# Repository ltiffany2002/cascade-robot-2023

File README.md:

# cascade-robot-2023
Code and PCB board for Cascade 2023 Robotics: Introduction to EE and Microcontrollers

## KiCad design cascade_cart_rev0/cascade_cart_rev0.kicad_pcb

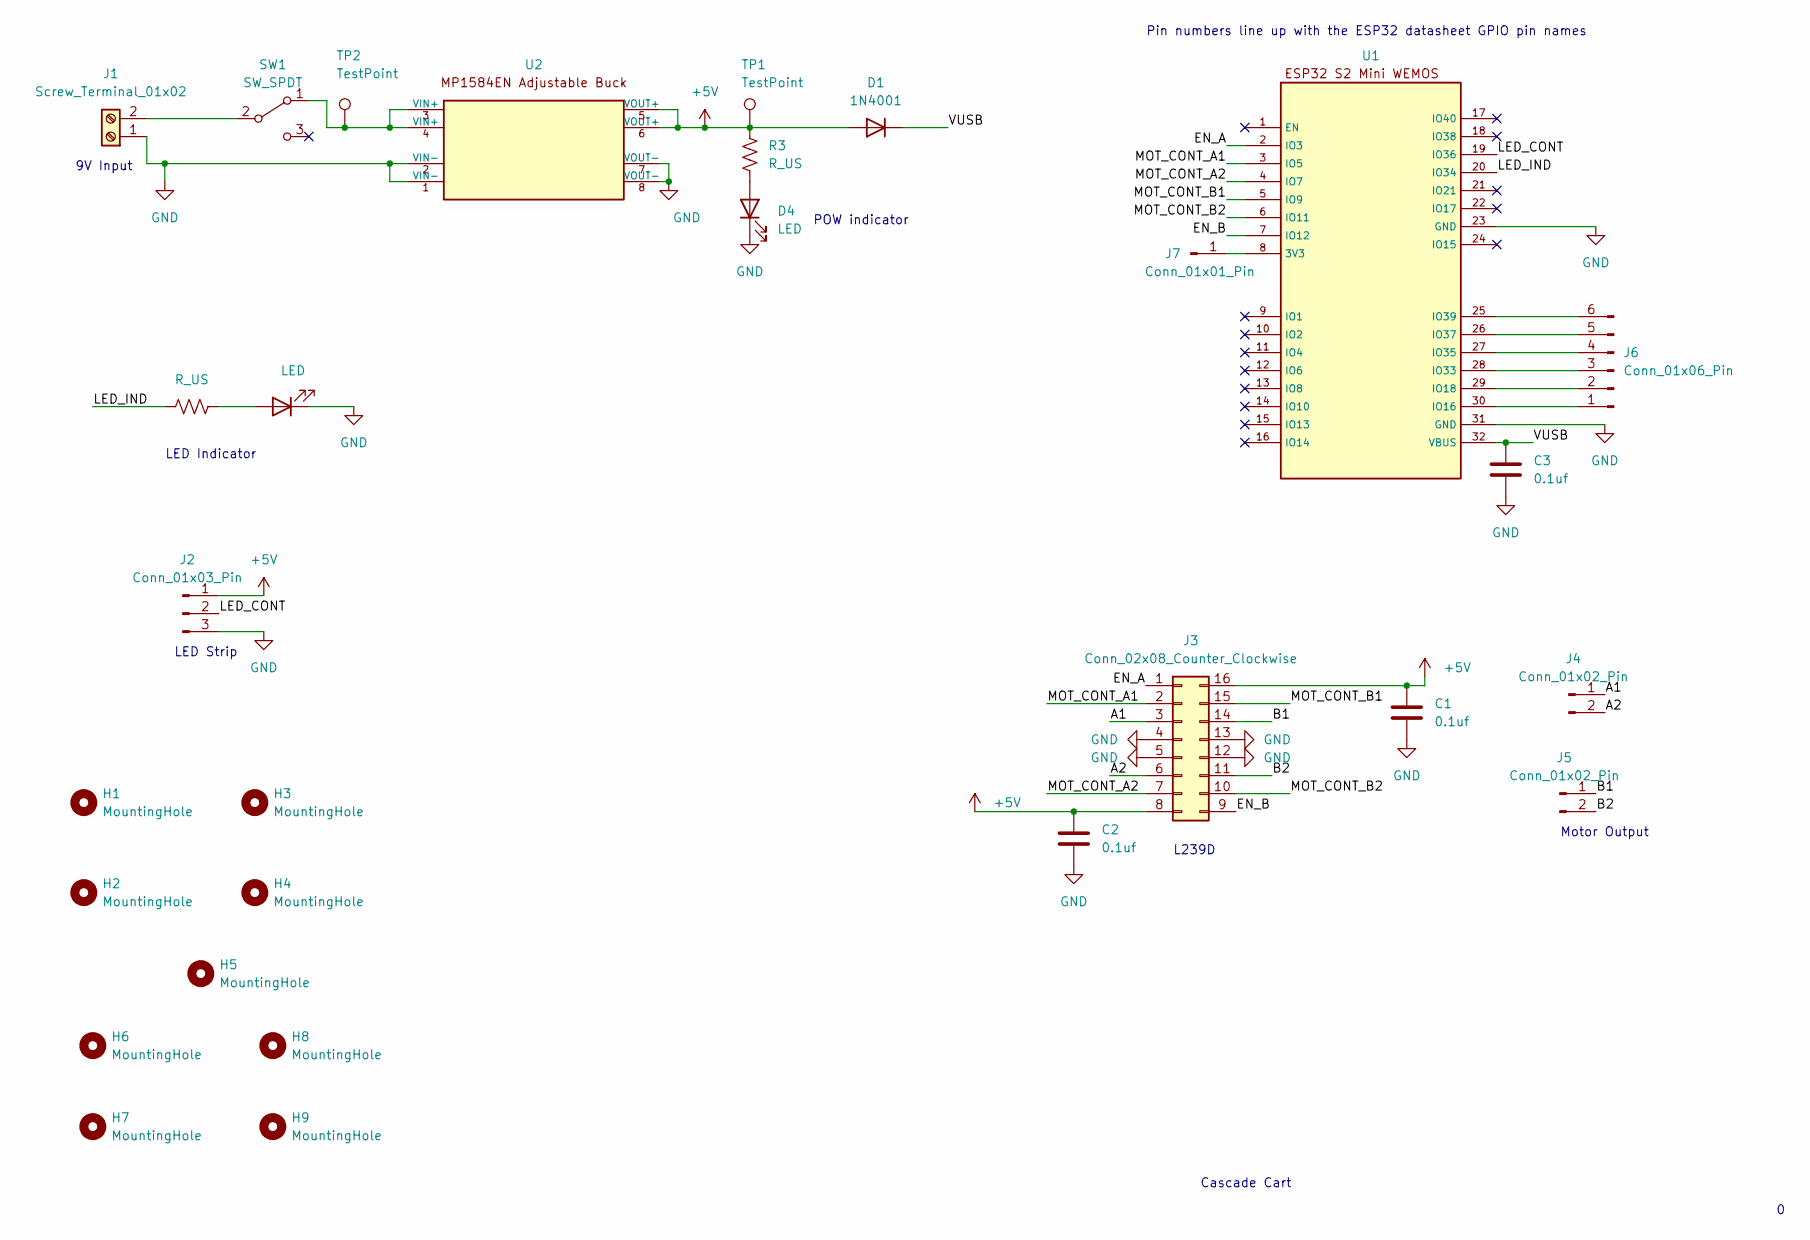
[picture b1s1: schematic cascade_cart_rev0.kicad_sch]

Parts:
C1, C2, C3: 0.1uf; C_Disc_D4.3mm_W1.9mm_P5.00mm
D1: 1N4001; D_DO-41_SOD81_P10.16mm_Horizontal
D3, D4: LED; LED_D5.0mm
H1, H2, H3, H4, H5, H6, H7, H8, H9: MountingHole; MountingHole_3.2mm_M3
J1: Screw_Terminal_01x02; PinHeader_1x02_P2.54mm_Vertical
J2: Conn_01x03_Pin; PinSocket_1x03_P2.54mm_Vertical
J3: Conn_02x08_Counter_Clockwise; 16-DIP Package
J4, J5: Conn_01x02_Pin; PinSocket_1x02_P2.54mm_Vertical
J6: Conn_01x06_Pin; PinHeader_1x06_P2.54mm_Vertical
J7: Conn_01x01_Pin; PinHeader_1x01_P2.54mm_Vertical
R2, R3: R_US; R_Axial_DIN0207_L6.3mm_D2.5mm_P10.16mm_Horizontal
SW1: SW_SPDT; PinSocket_1x03_P2.54mm_Vertical
TP1, TP2: TestPoint; TestPoint_Pad_D2.5mm
U1: esp32-s2-mini
U2: buck-breakout

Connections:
+5V: C1.1, C2.1, D1.2 (A), J2.1, J3.8, J3.16, R3.1, TP1.1, U2.5 (VOUT+), U2.6 (VOUT+)
/A1: J3.3, J4.1
/A2: J3.6, J4.2
/B1: J3.14, J5.1
/B2: J3.11, J5.2
/EN_A: J3.1, U1.2 (IO3)
/EN_B: J3.9, U1.7 (IO12)
/LED_CONT: J2.2, U1.19 (IO36)
/LED_IND: R2.1, U1.20 (IO34)
/MOT_CONT_A1: J3.2, U1.3 (IO5)
/MOT_CONT_A2: J3.7, U1.4 (IO7)
/MOT_CONT_B1: J3.15, U1.5 (IO9)
/MOT_CONT_B2: J3.10, U1.6 (IO11)
/VUSB: C3.1, D1.1 (K), U1.32 (VBUS)
GND: C1.2, C2.2, C3.2, D3.1 (K), D4.1 (K), J1.1, J2.3, J3.4, J3.5, J3.12, J3.13, U1.23 (GND), U1.31 (GND), U2.1 (VIN-), U2.2 (VIN-), U2.7 (VOUT-), U2.8 (VOUT-)
unnamed: D3.2 (A), R2.2
unnamed: D4.2 (A), R3.2
unnamed: J1.2, SW1.2 (B)
unnamed: J6.1, U1.30 (IO16)
unnamed: J6.2, U1.29 (IO18)
unnamed: J6.3, U1.28 (IO33)
unnamed: J6.4, U1.27 (IO35)
unnamed: J6.5, U1.26 (IO37)
unnamed: J6.6, U1.25 (IO39)
unnamed: J7.1, U1.8 (3V3)
unnamed: SW1.1 (A), TP2.1, U2.3 (VIN+), U2.4 (VIN+)

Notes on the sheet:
POW indicator
L239D
LED Indicator
Pin numbers line up with the ESP32 datasheet GPIO pin names
9V Input
Motor Output
LED Strip
Cascade Cart

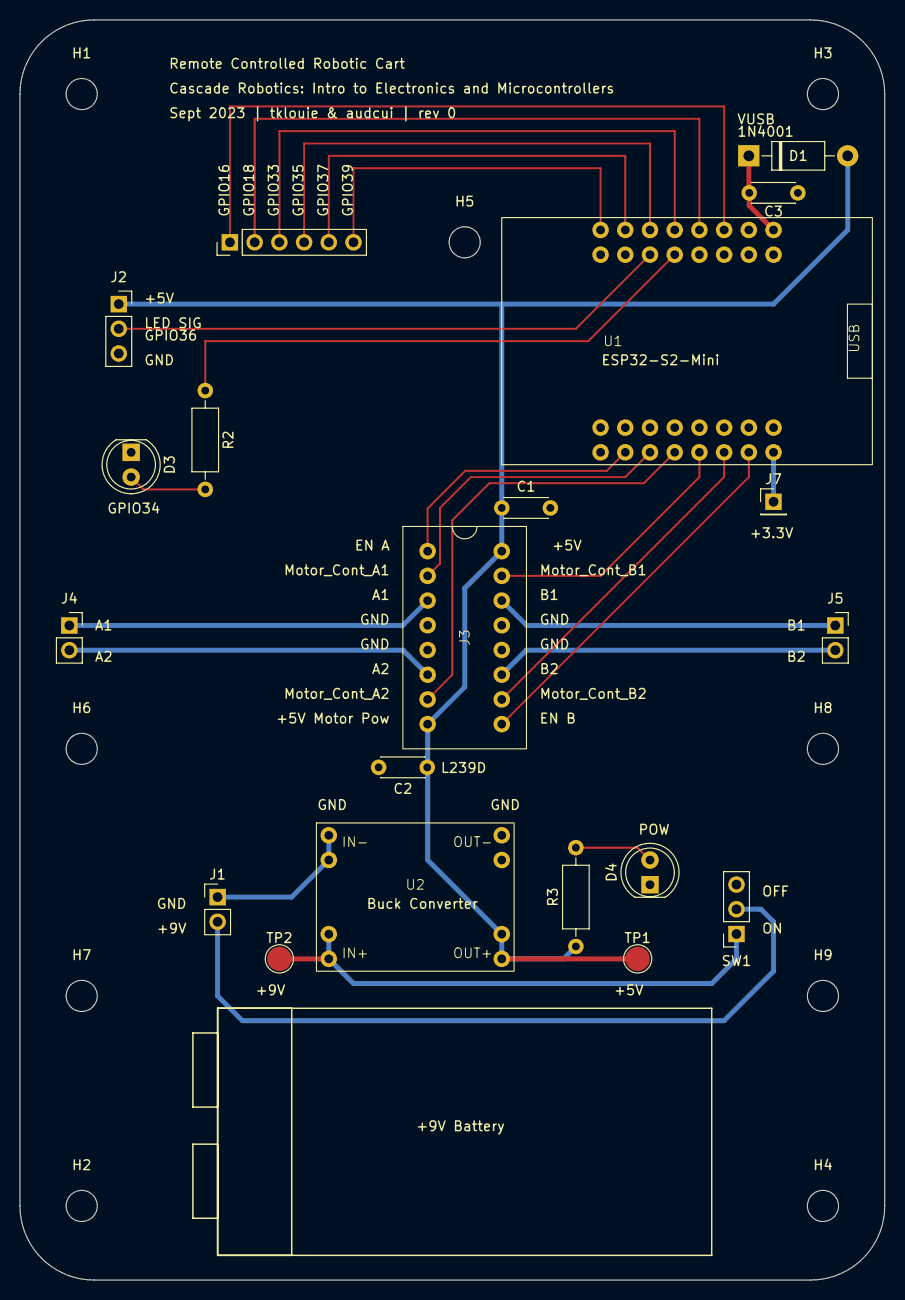
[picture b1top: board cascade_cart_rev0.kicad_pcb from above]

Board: 2 copper layers, 88.9 x 129.5 mm, 29 parts (0 on the bottom side), 26 nets.

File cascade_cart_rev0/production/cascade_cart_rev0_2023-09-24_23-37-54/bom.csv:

Designator,Footprint,Quantity,Value,LCSC Part #
"C1, C2, C3",C_Disc_D4.3mm_W1.9mm_P5.00mm,3,0.1uf,
D1,D_DO-41_SOD81_P10.16mm_Horizontal,1,1N4001,
"D3, D4",LED_D5.0mm,2,LED,
"H1, H2, H3, H4, H5, H6, H7, H8, H9",MountingHole_3.2mm_M3,9,MountingHole,
J1,PinHeader_1x02_P2.54mm_Vertical,1,Screw_Terminal_01x02,
J2,PinSocket_1x03_P2.54mm_Vertical,1,Conn_01x03_Pin,
J3,16-DIP Package,1,Conn_02x08_Counter_Clockwise,
"J4, J5",PinSocket_1x02_P2.54mm_Vertical,2,Conn_01x02_Pin,
J6,PinHeader_1x06_P2.54mm_Vertical,1,Conn_01x06_Pin,
J7,PinHeader_1x01_P2.54mm_Vertical,1,Conn_01x01_Pin,
"R2, R3",R_Axial_DIN0207_L6.3mm_D2.5mm_P10.16mm_Horizontal,2,R_US,
SW1,PinSocket_1x03_P2.54mm_Vertical,1,SW_SPDT,
"TP1, TP2",TestPoint_Pad_D2.5mm,2,TestPoint,
U1,esp32-s2-mini,1,~,
U2,buck-breakout,1,~,

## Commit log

2023-09-24 PCB Files
2023-09-24 fixing files
2023-09-24 adding reference arduino code
2023-09-24 update pcb
2023-09-30 prod files
2023-09-30 updating with pins
2023-10-28 adding example code files
